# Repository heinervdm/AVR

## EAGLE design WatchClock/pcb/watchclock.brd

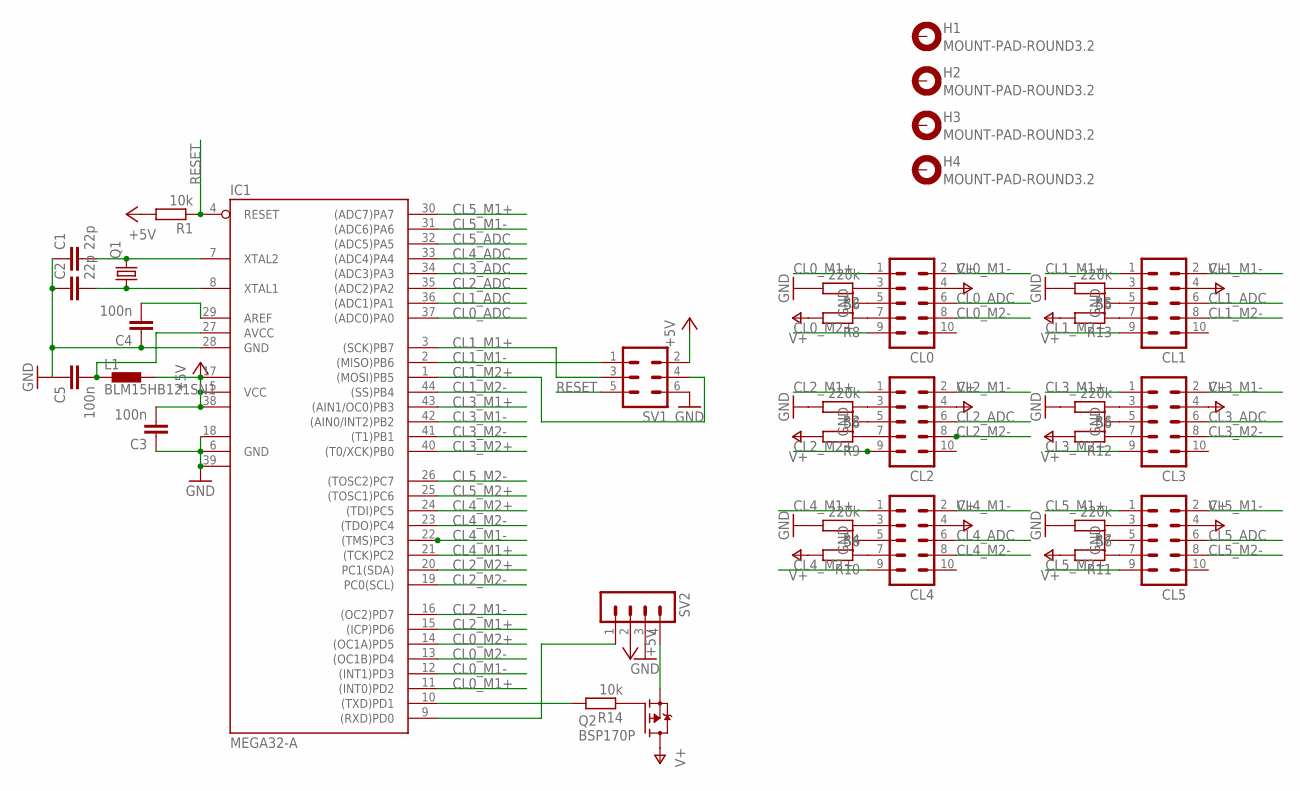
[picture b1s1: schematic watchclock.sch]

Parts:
C1, C2: 22p; C0805
C3, C4, C5: 100n; C0805
CL0, CL1, CL2, CL3, CL4, CL5: ML10
H1, H2, H3, H4: MOUNT-PAD-ROUND3.2; 3,2-PAD
IC1: MEGA32-A; TQFP44
L1: BLM15HB121SN1; 0402
Q1: CRYSTALHC49S; HC49/S
Q2: BSP170P; SOT223
R1, R14: 10k; M0805
R2, R3, R4, R5, R6, R7: 220k; M0805
R8, R9, R10, R11, R12, R13: 56; M0805
SV1: ML6
SV2: MA04-1

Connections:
+5V: C3.2, IC1.5 (VCC), IC1.17 (VCC1), IC1.38 (VCC2), L1.2, R1.2, SV1.2, SV2.2
CL0_ADC: CL0.6, IC1.37 ((ADC0)PA0)
CL0_M1+: CL0.1, IC1.11 ((INT0)PD2)
CL0_M1-: CL0.2, IC1.12 ((INT1)PD3)
CL0_M2+: CL0.9, IC1.14 ((OC1A)PD5)
CL0_M2-: CL0.8, IC1.13 ((OC1B)PD4)
CL1_ADC: CL1.6, IC1.36 ((ADC1)PA1)
CL1_M1+: CL1.1, IC1.3 ((SCK)PB7), SV1.3
CL1_M1-: CL1.2, IC1.2 ((MISO)PB6), SV1.1
CL1_M2+: CL1.9, IC1.1 ((MOSI)PB5), SV1.4
CL1_M2-: CL1.8, IC1.44 ((SS)PB4)
CL2_ADC: CL2.6, IC1.35 ((ADC2)PA2)
CL2_M1+: CL2.1, IC1.15 ((ICP)PD6)
CL2_M1-: CL2.2, IC1.16 ((OC2)PD7)
CL2_M2+: CL2.9, IC1.20 (PC1(SDA))
CL2_M2-: CL2.8, IC1.19 (PC0(SCL))
CL3_ADC: CL3.6, IC1.34 ((ADC3)PA3)
CL3_M1+: CL3.1, IC1.43 ((AIN1/OC0)PB3)
CL3_M1-: CL3.2, IC1.42 ((AIN0/INT2)PB2)
CL3_M2+: CL3.9, IC1.40 ((T0/XCK)PB0)
CL3_M2-: CL3.8, IC1.41 ((T1)PB1)
CL4_ADC: CL4.6, IC1.33 ((ADC4)PA4)
CL4_M1+: CL4.1, IC1.21 ((TCK)PC2)
CL4_M1-: CL4.2, IC1.22 ((TMS)PC3)
CL4_M2+: CL4.9, IC1.24 ((TDI)PC5)
CL4_M2-: CL4.8, IC1.23 ((TDO)PC4)
CL5_ADC: CL5.6, IC1.32 ((ADC5)PA5)
CL5_M1+: CL5.1, IC1.30 ((ADC7)PA7)
CL5_M1-: CL5.2, IC1.31 ((ADC6)PA6)
CL5_M2+: CL5.9, IC1.25 ((TOSC1)PC6)
CL5_M2-: CL5.8, IC1.26 ((TOSC2)PC7)
GND: C1.1, C2.1, C3.1, C4.1, C5.1, CL0.5, CL1.5, CL2.5, CL3.5, CL4.5, CL5.5, IC1.6 (GND), IC1.18 (GND1), IC1.28 (GND), IC1.39 (GND2), R2.2, R3.2, R4.2, R5.2, R6.2, R7.2, SV1.6, SV2.3
unnamed: CL0.3, R2.1
unnamed: C2.2, IC1.8 (XTAL1), Q1.1
unnamed: C1.2, IC1.7 (XTAL2), Q1.2
unnamed: C4.2, IC1.29 (AREF)
unnamed: C5.2, IC1.27 (AVCC), L1.1
unnamed: CL2.3, R3.1
unnamed: CL4.3, R4.1
unnamed: CL1.3, R5.1
unnamed: CL3.3, R6.1
unnamed: CL5.3, R7.1
unnamed: CL0.7, R8.1
unnamed: CL2.7, R9.1
unnamed: CL4.7, R10.1
unnamed: CL5.7, R11.1
unnamed: CL3.7, R12.1
unnamed: CL1.7, R13.1
unnamed: Q2.1 (G), R14.1
unnamed: Q2.3 (S), SV2.4
unnamed: IC1.10 ((TXD)PD1), R14.2
RESET: IC1.4 (RESET), R1.1, SV1.5
RXT: IC1.9 ((RXD)PD0), SV2.1
V+: CL0.4, CL1.4, CL2.4, CL3.4, CL4.4, CL5.4, Q2.2 (D), Q2.4 (D), R8.2, R9.2, R10.2, R11.2, R12.2, R13.2

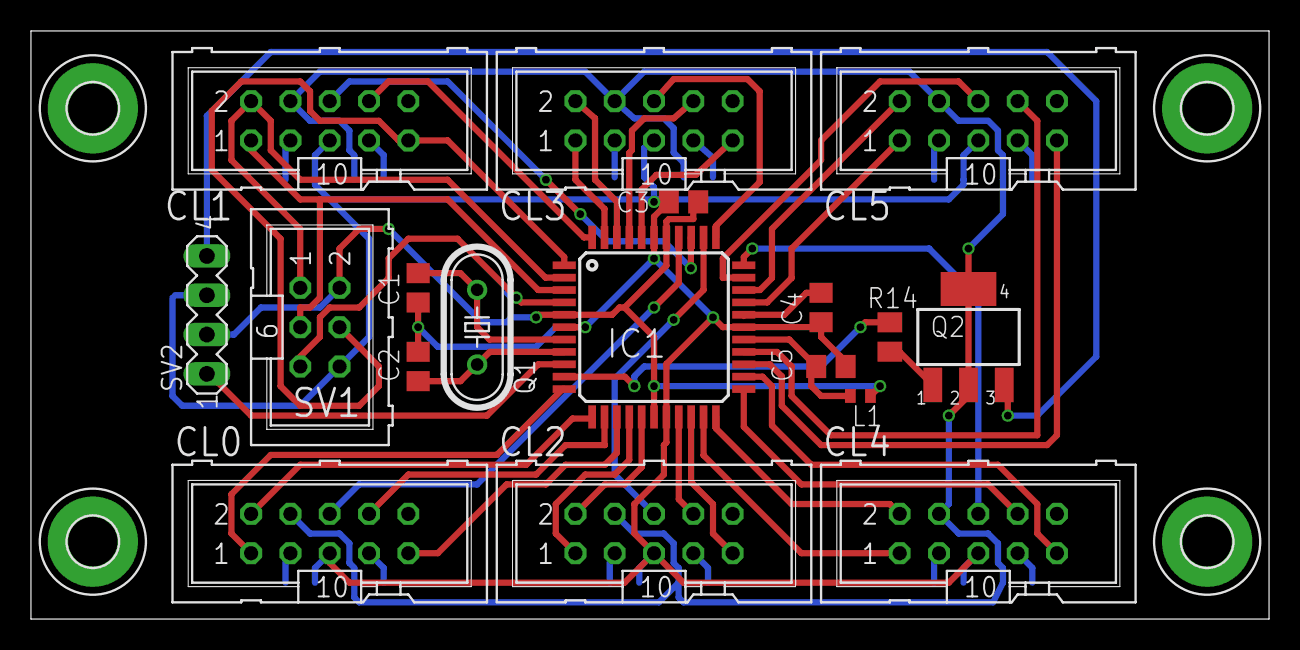
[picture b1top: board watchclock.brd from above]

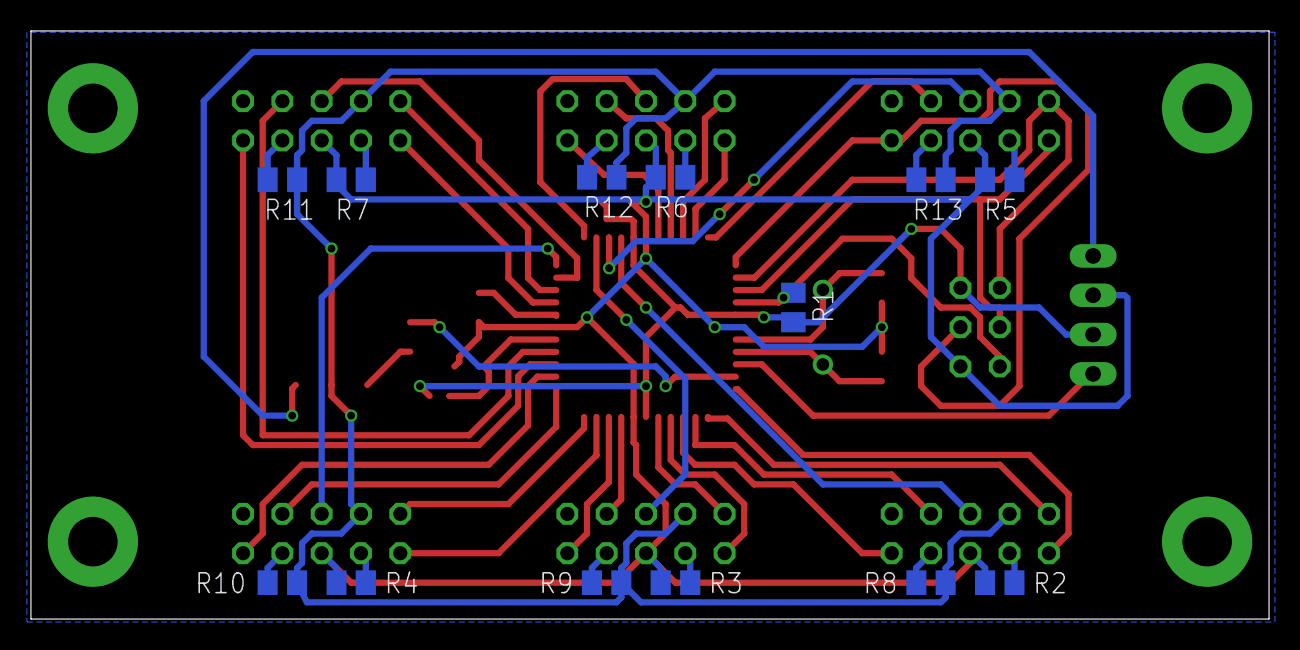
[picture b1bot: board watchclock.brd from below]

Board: 2 copper layers, 80.0 x 38.0 mm, 35 parts (13 on the bottom side), 54 nets.

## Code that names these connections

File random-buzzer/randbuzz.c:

#include <stdlib.h>
#include <stdint.h>
#include <avr/io.h>
#include <avr/interrupt.h>

#ifndef F_CPU
#define F_CPU           1000000                   // processor clock frequency
#warning kein F_CPU definiert
#endif

/************************************************************************/
/*                                                                      */
/*                      Debouncing 8 Keys                               */
/*                      Sampling 4 Times                                */
/*                      With Repeat Function                            */
/*                                                                      */
/*              Author: Peter Dannegger                                 */
/*                      danni@specs.de                                  */
/*                                                                      */
/************************************************************************/

#define KEY_DDR         DDRB
#define KEY_PORT        PORTB
#define KEY_PIN         PINB
#define KEY0            PB0
#define KEY1            PB1
#define KEY2            PB2
#define ALL_KEYS        (1<<KEY0 | 1<<KEY1 | 1<<KEY2)

#define REPEAT_MASK     (1<<KEY1 | 1<<KEY2)       // repeat: key1, key2
#define REPEAT_START    50                        // after 500ms
#define REPEAT_NEXT     20                        // every 200ms

volatile uint8_t key_state;                                // debounced and inverted key state:
// bit = 1: key pressed
volatile uint8_t key_press;                                // key press detect

volatile uint8_t key_rpt;                                  // key long press and repeat

///////////////////////////////////////////////////////////////////
//
// check if a key has been pressed. Each pressed key is reported
// only once
//
uint8_t get_key_press( uint8_t key_mask )
{
	cli();                                          // read and clear atomic !
	key_mask &= key_press;                          // read key(s)
	key_press ^= key_mask;                          // clear key(s)
	sei();
	return key_mask;
}

///////////////////////////////////////////////////////////////////
//
// check if a key has been pressed long enough such that the
// key repeat functionality kicks in. After a small setup delay
// the key is reported being pressed in subsequent calls
// to this function. This simulates the user repeatedly
// pressing and releasing the key.
//
uint8_t get_key_rpt( uint8_t key_mask )
{
	cli();                                          // read and clear atomic !
	key_mask &= key_rpt;                            // read key(s)
	key_rpt ^= key_mask;                            // clear key(s)
	sei();
	return key_mask;
}

///////////////////////////////////////////////////////////////////
//
// check if a key is pressed right now
//
uint8_t get_key_state( uint8_t key_mask )

{
	key_mask &= key_state;
	return key_mask;
}

///////////////////////////////////////////////////////////////////
//
uint8_t get_key_short( uint8_t key_mask )
{
	cli();                                          // read key state and key press atomic !
	return get_key_press( ~key_state & key_mask );
}

///////////////////////////////////////////////////////////////////
//
uint8_t get_key_long( uint8_t key_mask )
{
	return get_key_press( get_key_rpt( key_mask ));
}

///////////////////////////////////////////////////////////////////
// End debouncing functions
///////////////////////////////////////////////////////////////////

#define SOUND_DDR  DDRD
#define SOUND_PORT PORTD
#define SOUND_PIN  PIND
#define SOUND_OUT  PD5

#define STATUS_DDR  DDRD
#define STATUS_PORT PORTD
#define STATUS_PIN  PIND
#define STATUS_OUT  PD6

// SOUNDTIMEMAX in 0.01 seconds
#define SOUNDTIMEMAX 1000
// MAXRANDTIME 0 - 255 seconds
#define MAXRANDTIME 250

volatile uint32_t time = 0;
volatile uint16_t reactiontime = 0;
volatile uint8_t state = 0;
volatile uint16_t soundtime = 0;
volatile uint8_t playsound = 0;

uint8_t getRandom(uint8_t max) {
	return rand() / (RAND_MAX / max + 1);
}

void startSound(void) {
	playsound = 1;
	soundtime = 0;
	TIMSK |= (1<<OCIE1A);
	TCCR1B |= (1<<WGM12) | (1<<CS10) | (1<<CS12); // CTC, prescaler 1024
	OCR1A = F_CPU/1024/2000;
	STATUS_PORT |= (1<<STATUS_OUT);
}

void stopSound(void) {
	playsound = 0;
	TIMSK &= ~(1<<OCIE1A);
	SOUND_PORT &= ~(1<<SOUND_OUT);
	STATUS_PORT &= ~(1<<STATUS_OUT);
}

int main(void) {
	// Configure debouncing routines
	KEY_DDR &= ~ALL_KEYS;                // configure key port for input
	KEY_PORT |= ALL_KEYS;                // and turn on pull up resistors

	SOUND_DDR |= (1<<SOUND_OUT);
	STATUS_DDR |= (1<<STATUS_OUT);
	STATUS_PORT &= ~(1<<STATUS_OUT);

	TCCR0A = (1<<WGM01); // CTC Modus
	TCCR0B |= (1<<CS00) | (1<<CS02); // Prescaler 1204
	OCR0A = F_CPU/1024/100 + 1; // 100Hz
	TIMSK |= (1<<OCIE0A);
	sei();

	int8_t r = getRandom(MAXRANDTIME);
	while(1) {
		if (time/100 > r) {
			startSound();
		}
		if( get_key_press( 1<<KEY2 ) || get_key_rpt( 1<<KEY2 )){
			stopSound();
			r = getRandom(MAXRANDTIME);
			time = 0;
		}
	}
}

ISR (TIMER1_COMPA_vect) {
	if (soundtime < SOUNDTIMEMAX) {
		SOUND_PORT ^= (1<<SOUND_OUT);
		OCR1A = ((SOUNDTIMEMAX * 10) - (soundtime * 9))*F_CPU/1024/2000/SOUNDTIMEMAX;
	}
	else if (soundtime >= SOUNDTIMEMAX * 3 / 2) {
		startSound();
	} else {
		SOUND_PORT &= ~(1<<SOUND_OUT);
	}
}

ISR (TIMER0_COMPA_vect) {
	++time;

	if (playsound == 1) ++soundtime;

	static uint8_t ct0, ct1, rpt;
	uint8_t i;

	i = key_state ^ ~KEY_PIN;                       // key changed ?
	ct0 = ~( ct0 & i );                             // reset or count ct0
	ct1 = ct0 ^ (ct1 & i);                          // reset or count ct1
	i &= ct0 & ct1;                                 // count until roll over ?
	key_state ^= i;                                 // then toggle debounced state
	key_press |= key_state & i;                     // 0->1: key press detect
	
	if( (key_state & REPEAT_MASK) == 0 )            // check repeat function
		rpt = REPEAT_START;                         // start delay
	if( --rpt == 0 ){
		rpt = REPEAT_NEXT;                          // repeat delay
		key_rpt |= key_state & REPEAT_MASK;
	}
}

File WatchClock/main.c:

#include <avr/io.h>
#include <util/delay.h>
#include <avr/interrupt.h>
#include <avr/sleep.h>
#include <avr/power.h>

#include "uart.h"

#ifndef F_CPU
	#define F_CPU 3686400
#endif

#define UART_BAUD_RATE 9600L

/*
 * Clock mapping
 * -----
 * |0 1|
 * |2 3|
 * |4 5|
 * -----
 */

/*
 * Pointer mapping:
 * 0: clock 0, sec pointer
 * 1: clock 0, min pointer
 * 2: clock 1, sec pointer
 * 3: clock 1, min pointer
 * ...
 */
#define CLOCK_0_SEC 0
#define CLOCK_0_MIN 1
#define CLOCK_1_SEC 2
#define CLOCK_1_MIN 3
#define CLOCK_2_SEC 4
#define CLOCK_2_MIN 5
#define CLOCK_3_SEC 6
#define CLOCK_3_MIN 7
#define CLOCK_4_SEC 8
#define CLOCK_4_MIN 9
#define CLOCK_5_SEC 10
#define CLOCK_5_MIN 11

#define BACKUPSTEPS 7

/*
 * Index mapping:
 * pointer 0: pin 1 -> 0, pin 2 -> 1
 * pointer 1: pin 1 -> 2, pin 2 -> 3
 * ...
 * pointer i: pin1 -> i*2, pin 2 -> i*2 + 1
 */
// FIXME: extend this to 12
#define N_POINTERS 2
// FIXME: extend these to 24
// first seconds pointer then minutes pointer of one clock
volatile uint8_t *ports[N_POINTERS*2]      = {&PORTD,&PORTD,&PORTD,&PORTD};
volatile uint8_t *ddrs[N_POINTERS*2]       = {&DDRD, &DDRD, &DDRD, &DDRD};
const uint8_t pins[N_POINTERS*2]           = {PD6,   PD7,   PD2,   PD3};
// FIXME: extend this to 6
// 2 pointers share one ADC
const uint8_t adcs[N_POINTERS/2]        = {0};
// FIXME: extend these to 12
const uint8_t stepsPerSec[N_POINTERS]   = { 1, 4};
uint8_t position[N_POINTERS]            = { 0, 0};
const uint8_t zeroSteps[N_POINTERS]     = { 5,14};
const uint8_t stepsAfterZero[N_POINTERS]= { 5, 7};

const uint8_t times[10][6][2] = {
	{{30,15*4},{45,30*4},{ 0,30*4},{ 0,30*4},{ 0,15*5},{ 0,45*4}}, // 0
	{{37,37*4},{30,30*4},{37,37*4},{ 0,30*4},{37,37*4},{ 0, 0*4}}, // 1
	{{15,15*4},{45,30*4},{15,30*4},{45, 0*4},{ 0,15*4},{45,45*4}}, // 2
	{{15,15*4},{45,30*4},{15,15*4},{45,30*4},{15,15*4},{45, 0*4}}, // 3
	{{30,30*4},{30,30*4},{ 0,15*4},{ 0,45*4},{37,37*4},{ 0, 0*4}}, // 4
	{{15,30*4},{45,45*4},{ 0,15*4},{45,30*4},{15,15*4},{45, 0*4}}, // 5
	{{15,30*4},{45,45*4},{30,15*4},{45,30*4},{ 0,15*4},{ 0,45*4}}, // 6
	{{15,15*4},{15,30*4},{37,37*4},{ 0,37*4},{ 7,37*4},{37,37*4}}, // 7
	{{30,15*4},{30,45*4},{30,15*4},{30,45*4},{ 0,15*4},{ 0,45*4}}, // 8
	{{30,15*4},{30,45*4},{ 0,15*4},{ 0,45*4},{15,15*4},{ 0,45*4}}, // 9
};

const uint8_t digit = 0;

volatile uint8_t duration = 0;
uint16_t lastpulse = 0; // bit = 0 -> lastpulse pin 0, bit = 1 -> lastpulse pin 1

uint8_t uart_data;

void pulse(uint16_t pointers) {
	for (uint8_t i = 0; i < N_POINTERS; i++) {
 		if (pointers & (1<<i)) {
			uint8_t index = i*2;
			uint8_t oindex = index;
			if (lastpulse & (1<<i)) {
				index += 1;
			} else {
				oindex += 1;
			}
			*ports[index] |= (1<<pins[index]);
			*ddrs[index]  |= (1<<pins[index]);
			*ddrs[oindex] |= (1<<pins[oindex]);
			lastpulse ^= (1<<i);
			position[i]++;
			if (position[i] >= 60*stepsPerSec[i]) position[i] = 0;
		}
	}
	duration = 1;
	TIMSK |= (1<<OCIE2);       // TC0 compare match A interrupt enable
}

void init(void) {
// 	power_adc_enable();
	PORTB &= ~(1<<PB0);
	DDRB |= (1<<PB0);
	uint16_t p = 0;
	uint8_t zerostepcount[N_POINTERS];
	uint8_t stepsToGo[N_POINTERS];
	uint8_t backupstepsgone[N_POINTERS/2];
	uint16_t zeroFound = 0;
	for (uint8_t i = 0; i < N_POINTERS; i++) {
		zerostepcount[i] = 0;
		stepsToGo[i] = stepsAfterZero[i];
		if (i<N_POINTERS/2) {
			backupstepsgone[i] = 0;
		}
	}
	// home minutes first, because it's more likley to cover the lightbarrier with the minutes pointer
	uint8_t minutesHomed = 1;
	while (1) {
		p = 0;
		for (uint8_t i = minutesHomed; i < N_POINTERS; i+=2) {
			if (minutesHomed == 1 && zerostepcount[i] > 20) {
				// move minutes pointer away
				if (backupstepsgone[i/2] < BACKUPSTEPS) {
					backupstepsgone[i/2]++;
					p |= (1<<(i-1));
				} else {
					backupstepsgone[i/2] = 0;
					zerostepcount[i] = 0;
				}
			}
			if (minutesHomed == 0 || zerostepcount[i] <= 20) {
				ADMUX = (1<<REFS0) | (1<<REFS1) | (adcs[i/2] & 0x0F);
				ADCSRA = (1<<ADEN) | (1<<ADSC);
				while (ADCSRA & (1<<ADSC));
				uint16_t ares = ADCL;
				ares += (ADCH<<8);
				// 0.1V*1024/2.56V = 40
				uart_puts("ADC: ");
				uart_putc(ares/1000+'0');
				uart_putc(ares%1000/100+'0');
				uart_putc(ares%100/10+'0');
				uart_putc(ares%10+'0');
				uart_putc('\n');
				if (ares < 150) {
					// LED off
					zerostepcount[i]++;
					PORTB |= (1<<PB0);
				}
				else {
					// LED on
					PORTB &= ~(1<<PB0);
					if (zerostepcount[i] == zeroSteps[i]) {
						// LED was off for the searched time -> we found the zero position
						zeroFound |= (1<<i);
					}
					zerostepcount[i] = 0;
				}
				if (stepsToGo[i] > 0) {
					p |= (1<<i);
					// zero was found, go the remaining steps to zero position
					if (zeroFound & (1<<i)) stepsToGo[i]--;
				}
				ADCSRA = 0;
			}
		}
		if (p > 0) {
			pulse(p);
			while(duration > 0); // wait for pulse to finish, can go to sleep mode in this time
// 			set_sleep_mode(SLEEP_MODE_IDLE);
// 			sleep_mode();
		} else {
			if (minutesHomed == 0) break;
			else minutesHomed = 0;
		}
	}
// 	power_adc_disable();
}

int main(void) {
	uint8_t timeReached = 1;
// 	power_all_disable();
// 	power_timer2_enable();
// 	power_usart0_enable();
// 	wdt_disable();
	DDRD = 0; // All inputs
	PORTD = 0; // All PullUps off

	// interrupt for motor pulses
	OCR2  = (F_CPU/(1024*20))/4; // number to count up to 50ms/4
	TCCR2 = (1<<WGM21);          // Clear Timer on Compare Match (CTC) mode
	TCCR2 = (1<<CS20)|(1<<CS21)|(1<<CS22); // clock source CLK/1024

	uart_init( UART_BAUD_SELECT(UART_BAUD_RATE,F_CPU) ); 

	sei();
	init();
	for (uint8_t i = 0; i < N_POINTERS; i++) {
		position[i] = 0;
	}
	uart_puts("Start main loop.\n");
	while(1) {
		if (timeReached == 1) {
			set_sleep_mode(SLEEP_MODE_IDLE);
// 			power_timer2_disable();
// 			sleep_enable();
// 			sleep_bod_disable();
// 			sleep_cpu();
// 			sleep_disable();
			_delay_ms(100);
// 			power_timer2_enable();
		} else {
			uint16_t p = 0;
			uart_puts("Current Position: ");
			for (uint8_t i = 0; i < N_POINTERS; i++) {
				if (i > 0) uart_putc(',');
				uart_putc(i+'0');
				uart_puts(": ");
				uart_putc(position[i]/100+'0');
				uart_putc(position[i]%100/10+'0');
				uart_putc(position[i]%10+'0');
				uart_puts(" (");
				uart_putc(times[uart_data-'0'][i/2][i%2]/100+'0');
				uart_putc(times[uart_data-'0'][i/2][i%2]%100/10+'0');
				uart_putc(times[uart_data-'0'][i/2][i%2]%10+'0');
				uart_puts(")\n");
				if (position[i] != times[uart_data-'0'][i/2][i%2]) {
					p |= (1<<i);
				}
			}
			if (p > 0) {
				uart_puts("pulse\n");
				pulse(p);
				while(duration > 0); // wait for pulse to finish, can go to sleep mode in this time
			} else {
				uart_puts("time reached\n");
				timeReached = 1;
			}
		}
		_delay_ms(100);

		uint16_t c = uart_getc();
		if (! (c & UART_NO_DATA) ) {
			if (c >= '0' && c <= '9') {
				uart_data = c & 0xFF;
				timeReached = 0;
				uart_puts("New position: ");
				uart_putc(uart_data);
				uart_putc('\n');
			}
		}
	}
}

ISR(TIMER2_COMP_vect ) {
	cli();
	++duration;
	if (duration > 4) {
		// all pulses stop
		DDRD = 0;
		PORTD = 0;
		duration = 0;
		TIMSK &= ~(1<<OCIE2);
	}
	sei();
}

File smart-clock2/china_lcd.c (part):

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 * I wired the LCD as follows:
 * VCC      +5V
 * GND      GND
 * SCL      PB5 (SCK), Digital Pin 13 on Arduino
 * SDA      PB3 (MOSI), Digital Pin 11 on Arduino
 * RS       PD7, Digital Pin 7 on Arduino
 * RST      PD6, Digital Pin 6 on Arduino
 * CS       GND
 *
 * I wired CS to GND because this is the only SPI device in my current
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
/********************** START SPI STUFF *********************************/
void SPI_begin(void) {
    DDRB |= (1 << PB5);//out
    DDRB |= (1 << PB3);//out
    DDRB |= (1 << PB2);//out

    PORTB &= ~(1 << PB5);//lo
    PORTB &= ~(1 << PB3);//lo
    PORTB |= (1 << PB2);//hi

    SPCR |= (1 << MSTR) | (1 << SPE);
}
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
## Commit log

2013-07-23 Add smart-clock2 files
2013-07-23 Add functions to read rtc and add lib for temp sensor
2013-07-23 Remove unused eclipse files
2013-07-24 Read temperature sensor and print propper time and date
2013-07-24 Enable 1Hz clock of ds1307 and enable sleep if dcf is not synchronizing
2013-07-24 Remove unused delacrations of time and newtime
2013-07-24 Port to atmega328p
2013-07-24 Update rtctime after sucessfull dcf sync
2013-07-24 Update pins, use clockselect pin of lcd
2013-07-24 Update time and date strings and set correct font size and positions
2013-07-24 Use hardware i2c and fix display of time
2013-07-25 Read DS1307 clock bits correctly
2013-07-25 Set 24h bit if not set
2013-07-25 Fix ds1307_settime() set time in bcd format
2013-07-26 Put ds1307 functions in extra file
2013-07-26 measure temperature before going into the mainloop, so that the temperature will be measured before the dcf77 sync
2013-07-26 Use pointers instead of global variables
2013-07-26 Add and use ds1307_init() and ds1307_sqw() functions
2013-07-26 Enable Interrupt on rsing edge on INT0
2013-07-26 Add test script to plot all chars in glcdfont.c
2013-07-26 Work around missing ° in glcdfont.c
2013-07-26 Clean up wrong merge
2013-07-26 Set clock enable bit of ds1307 if not set
2013-07-26 Fix ds1307_settime
2013-07-26 Add alternative ds18b20 sensor library
2013-07-26 commit out temperature reading, as it's not working
2013-08-13 Add Watchdog
2013-08-13 Add correct interrupt vector
2013-12-15 Add new project, random buzzer
2013-12-18 random-buzzer: first working version
2014-01-05 random-buzzer: add kind of one bit sound.
2015-05-09 Add first steps of WatchClock
2015-05-17 WatchClock: switch to atmega8, implement homeing functionallity
2015-06-08 Add WatchClock PCB
2015-06-14 WatchClock PCB: Routing complete
2015-06-15 Update WatchClock PCB
2015-06-20 watchClock: first working homeing code and updated pcb
2015-06-23 WatchClock: Working prototype firmware for atmega8
2015-06-23 watchClock: add demonstration video and picture of the clock modifications
2016-05-29 Add simple fan temperture control
2016-05-29 Switch pins for temperature and fan
2016-05-29 Start with 50% PWM
2016-05-29 Start fan at 35deg
2016-06-26 Add first version of an electronic cricket, based on http://www.avrprojects.net/index.php/avr-projects/sound/39-electronic-cricket
2016-06-26 use timer instead of delay and add pin change interrupt
2016-06-26 prepare for random sleep time
2016-06-30 use delays for testing first
